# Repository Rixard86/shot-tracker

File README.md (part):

# ShotPuck: automatic arrow counter for Avalon barebow riser weights

A Ø40 × 10.4 mm puck that bolts onto the free face of an Avalon riser weight (the weight's own 5/16-24 bolt, one size longer, goes through its centre), detects each shot with a 6-axis IMU, records the bow's motion around it (accelerometer + gyroscope, 1.0 s before to 0.5 s after release), and reports both over BLE to the scoring app.

| | |
|---|---|
| Size / mass | Ø40 mm (= the Avalon barebow weight's diameter), 10.43 mm above the weight face (2.0 mm flat aluminium plate; the 1.2 mm PCB on 3 mm standoffs, the cell in a notch in the PCB), 17.1 g, centre of mass 0.5 mm off axis (no trim weight); 1.6 mm free space above the cell |
| Radio / MCU | u-blox BMD-340 (nRF52840, 1 MB flash / 256 KB RAM, PCB antenna), BLE 5 |
| Sensor | ST LSM6DSV32X IMU: 480 Hz, ±32 g accelerometer + ±2000 dps gyroscope while active; accelerometer only, 15 Hz wake-on-motion, while idle |
| Battery | LIR1254 Li-ion coin, 45–65 mAh, plain (no tabs) on spring contacts, protected by TI BQ29700 + DMN2004DWK; charged through a waterproof (IPX8) side-entry USB-C port, power only (21 mA, temperature-gated) |
| Firmware | Zephyr 4.1, custom board `shotpuck/nrf52840`, MCUboot 28 KB + signed app 201 KB (256 KB slots) / 107 KB RAM (58 KB of it the capture ring); captures compressed into a 408 KB flash area (D31) |
| Updates | Over the air: MCUboot with ECDSA-P256 signed images and automatic rollback, MCUmgr/SMP over BLE for paired phones, 10 s watchdog |
| Security / sync | Pairing required (LE Secure Connections); new phones only within 60 s of attaching the charger, which the advertising data signals so the app pairs by itself; links that do not encrypt within 30 s are dropped. Last ~900 shots kept in flash for replay. |

## Repository

```
layout.json                 shared geometry: CAD and PCB both read it
firmware/                   Zephyr app (src/, boards/shotpuck/, prj.conf, debug.conf)
firmware/sim/               Monte Carlo validation of src/shot_detect.c, unit tests of capture.c, evlog.c, chg_led.c, recovery.c, led_seq.c, wire.c, evq.c, the capture codec and store, and an end-to-end capture test (+ results.txt)
firmware/VERSION            firmware version (signed into the OTA image, shown in DIS and STATUS)
firmware/sysbuild.*         MCUboot + signing setup (refuses MCUboot's public dev key)
firmware/shotpuck_full.hex  MCUboot + signed app, for the first flash via the SWD test pads
firmware/shotpuck_update.bin  signed app image for OTA updates
hardware/design.py          the circuit (single source of truth)
hardware/design_mini.py     ShotPuck mini circuit: 33 x 33 mm square board for a Picatinny-rail case, CR2450 on the back
hardware/gen_sch.py         -> kicad/shotpuck.kicad_sch (`gen_sch.py design_mini` -> kicad/shotpuck-mini.kicad_sch)
hardware/check_netlist.py   KiCad netlist vs design.py (`check_netlist.py design_mini` for the mini)
hardware/gen_pcb.py         -> kicad/shotpuck.kicad_pcb (place, keep-outs, route, DRC)
hardware/gen_mini_pcb.py    -> kicad/shotpuck-mini.kicad_pcb (outline, CR2450 clip footprint, parts placed,
                            antenna keep-out, GND pours; unrouted, routed by hand, never overwritten)
hardware/board_shape.py     board outline, cell notch, bolt hole and antenna zone (shapely, from layout.json)
hardware/islands.py         post-fill GND island bridging used by gen_pcb.py
hardware/gen_bom.py         -> kicad/fab/shotpuck-bom.csv
hardware/gen_panel.py       -> kicad/panel/shotpuck-panel.kicad_pcb (1x2 KiKit panel for JLCPCB)
hardware/gen_jlc.py         -> kicad/fab/jlc/ (JLCPCB assembly BOM + CPL with LCSC part numbers, rotated/shifted to JLC's footprints)
hardware/bmd340.py          u-blox BMD-340 footprint, 3D model placement and schematic symbol (from its data sheet)
hardware/hotplug_sim.py     USB-C hot-plug simulation of the charge input, 324-case sweep (`--rev-0a`: R9 fed from VIN)
hardware/kicad/             KiCad project, ShotPuck.pretty/.kicad_sym/.3dshapes, schematic PDF, fab/ (gerbers, drill, pos, BOM)
mechanical/puck.py          CadQuery model + mass/balance -> out/ (STEP, STL, mass_report.txt);
                            geometry.py, puck_parts.py, puck_report.py hold its constants, parts and output
mechanical/plate_drawing.py plate manufacturing drawing (hole table, M2 thread callout) -> out/plate_drawing.pdf;
                            5052 sheet-metal prototype variant -> out/plate_drawing_5052.pdf + out/plate_5052.step
mechanical/plate_fdm.py     3D-printable (FDM) plate: locating lip instead of the O-ring, cell pocket, tube lip -> out/plate_fdm.stl
mechanical/viewer/          3D viewer of the rev 0A puck: assembled-to-exploded slider, cut view, cap seal band old/new
                            (three.js, one index.html with the meshes and the PCB embedded); also the private artifact claude.ai/artifact/EnhZPnRmLfCq5PVbHscZpo
mechanical/blender/         Blender scene + exploded-view assembly animation -> out/shotpuck_assembly.mp4/.blend
docs/PROTOCOL.md            BLE GATT protocol for the app
docs/VALIDATION.md          what is proven, and the on-device checklist
order/                      order packages for JLC (PCB + assembly, plate, cap), each with an ORDER.md:
                            form settings, notes for the order and the checks against JLC's rules
```

## Decisions (change any, then re-run the generators)

| # | Decision | Why | Alternative |
|---|---|---|---|
| D1 | **Cell beside the module, no trim weight** | Module at the upper right, bolt in the middle, cell in a notch at the bottom. The centre of mass is 0.5 mm off axis (≈ 0.01 mm on a 2 kg bow); Richard dropped the optional brass pin when the PCB went up on standoffs | Two LIR1254 side by side (studied: they cut the board in two); a brass trim pin |
| D2 | **Flat 6061 plate (2.0 mm) + polycarbonate cap, bolted on through a steel sleeve** | Richard: the v0.2 stud could not be fitted to the bow (it needs a bolt from above), and a flat plate is cheaper (laser or waterjet, no turning). The sleeve carries the bolt's clamp load to the plate; on the prototype the PC cap top sits between the bolt head and the sleeve (D21) | Turned 7075 base with an integral stud (v0.2) |
| D3 | **nRF52840 in high-voltage mode** (cell → VDDH, REG0 = 3.0 V) | No regulator, no battery divider (internal VDDH/5), fewer leaks | External LDO |
| D4 | **MCP73831 + firmware temperature gate** (nRF die temperature, <1 °C / >44 °C) | MCP73831 programs down to 15 mA; the TS-pin chargers found start at 100 mA. Default is *charging allowed* if the MCU is dead, so a flat cell always recovers. | Charger with an NTC input and a thermistor at the cell |
| D5 | **32 kHz from internal RC; REG1 in DC/DC mode in the app (0.3.1), REG0 and MCUboot in LDO mode** | The BMD-340 has no 32.768 kHz crystal. Its data sheet (UBX-19033353 §3.3) puts an LDO and a DC/DC converter with no external parts in both regulator stages, and DC/DC about halves the CPU and radio current. REG0 also feeds the IMU, so it stays LDO until its noise is checked; MCUboot stays LDO so an OTA image with DC/DC can roll back | All LDO (0.3.0); DC/DC on REG0 as well |
| D6 | **Plain LIR1254 (no tabs) on contacts:** a + spring against the can side and a − strap over the top cap, soldered to two SMD pads left of the notch; the cap's foam pad clamps the cell and the strap | Richard's choice: no tab variant to source, no soldering on the cell, swappable | Tabbed LIR1254 soldered to pads; 601015 pouch (closed-ring board, ~9.9 mm) |
| D7 | **Pairing required; new pairings only within 60 s of attaching the charger** (LE Secure Connections Just Works, up to 4 phones, FORGET_BONDS to reset) | Several pucks and shooters at one club: other apps must not read, reconfigure or reset your puck. The charger gesture proves physical possession. | Open access (v1), or a PIN shown by LED blinks |
| D8 | **Detector thresholds are defaults, tunable over BLE**; every candidate is reported | Real release-shock data is unknown until you shoot | – |
| D9 | IMU rotated 270°, reference designators on F.Fab only | Routability; board too dense for silkscreen text | – |
| D10 | **LSM6DSV32X IMU** (LSM6DSV32XTR, C22461202, since 2026-10-01; v0.2 used the LSM6DSO32, which replaced the LIS2DE12 accelerometer). Same LGA-14 pinout and land pattern as the LSM6DSO32, so the board is unchanged; JLC's footprint lands within 0.013 mm of ours at 0°. Pinout, pin states and register values checked against datasheet DS13511 Rev 2 and ST's `lsm6dsv32x_reg.h`. It has no separate I3C disable, so the I²C anti-spike filter is forced on at init (`IF_CFG.ASF_CTRL`), as the datasheet describes for I²C-only use. It has no 416 Hz rate: ACTIVE runs at 480 Hz | Gyroscope for bow rotation; ±32 g clips the release shock less; 2.75× lower accelerometer noise than the LSM6DSO32 at ±32 g (80 against 220 µg/√Hz) and lower gyroscope noise (2.8 against 3.8 mdps/√Hz); ±4000 dps available; 5,864 in JLC stock against 177 | LSM6DSO32XTR (C3663738): 416 Hz, twice the FIFO (3 KB uncompressed), 0.1 mA less while active |
| D11 | **Raw 6-axis capture per accepted shot** (standard −1.0 s to +0.5 s, 720 samples, 8.6 KB raw; extended −6 s to +2 s, D31), analysed in the app | Which bow-movement metrics matter is unknown until real shots are recorded | On-device metrics (cant, steadiness, post-release rotation) in the EVENT |
| D12 | **Identity from the chip's factory ID**: name `ShotPuck-XXXX`, DIS serial number = `device_id` | Tell pucks apart at a club; one stable ID across phones for PowerSync | App-assigned IDs |
| D13 | **Accepted shots in a 32 KB flash ring** (~900 shots), rejected candidates in RAM; app-driven REPLAY, sent paced in the background | Shots survive dropouts and resets without per-phone sync state on the puck | Device push with ACK (rejected: shared state, first phone drains the backlog); captures in flash too |
| D14 | **u-blox BMD-340-A-R (nRF52840) instead of the Raytac MDBT50Q-1MV2**: 15.0 × 10.2 × 1.9 mm LGA-68, PCB antenna, VCCH input for high-voltage mode, FCC/CE/Bluetooth certified. Footprint `ShotPuck:u-blox_BMD-340` from data sheet UBX-19033353 (Figure 12), checked pad for pad against two built open-source footprints | Richard: replace parts JLCPCB does not stock. On 2026-09-29 JLCPCB had 0 MDBT50Q-1MV2 and 227–393 BMD-340 (C5456944, $8.73 vs $18.93). nRF52840 kept for the two OTA slots (2 × 460 KB). **Only type BMD-340-A-R-10 is usable:** -00 (nRF52840 rev 1) has a non-functional high-voltage mode, so confirm the type with JLCPCB before ordering | MDBT50Q-1MV2 via global sourcing or consignment; u-blox NINA-B306 ($20, 59 in stock) |
| D16 | **Cell protection (PCM): TI BQ29700 + Diodes DMN2004DWK** in the cell's negative lead (OVP 4.275 V, UVP 2.80 V, ±0.1 A over-current, short-circuit) | LIR cells have no protection of their own; kept from the CP1654 design (BQ29700 was on Varta's list). Costs 4 µA standby | – |
| D17 | **1.6 mm free space above the cell** (7.0 mm from the Kapton to the ceiling) | No swell spec for LIR cells. It was 1.2 mm (set on the magnetic board so its connector was flush with the cap top, D25) until the PCB went to 1.2 mm (D30): the ceiling rose 0.4 mm with the board, so the free space is now above Varta's 1.5 mm. The foam pad fills it | 1.2 mm with 2.6 mm standoffs (non-stock) |
| D19 | **Board Ø36 mm; 4× M2×8 cheese head (Torx) screws from above, all at r = 16.5 mm: H1 100.6°, H2 164.5°, H3 305°, H4 226°**, through the cap, PCB and standoffs into the tapped plate | Puck Ø40 mm is fixed by the Avalon weight; 36 leaves 0.5 mm fit clearance. The screws sit clear of the module, the cell notch and the port. H1 and H2 sit either side of the USB-C port, far enough apart that the ground pour reaches J1's wing tabs; H4 holds the left arm (D29). The 1.3 mm head lets an M2×8 end 0.1 mm inside the plate (a socket head would need the non-standard M2×7). Since 2026-10-12 the screws are M2×5 into brass male-female standoffs screwed into the plate; the cap keeps the M2×8 counterbore | – |
| D20 | **Cell in a notch in the PCB, open to the rim** (Ø13.0 mm round end), on the Kapton over the plate | Saves the 0.8 mm board in height. Richard preferred the notch to a closed hole | Closed hole (holds the cell all round, leaves a thin strip at the rim) |
| D18 | **Waterproof (IPX8) side-entry USB-C, SHOU HAN TYPE-C 6PFS 2JCB1.6-H6.7 IPX8** (6-pin, power only, LCSC C3020041, JLC-assembled) at 132.58° on the left rim, recessed in a notch in the board edge, plug axis radial through the cap wall; R10/R11 5.1k pull CC1/CC2 down | Richard (2026-09-30). Any USB-C charger and cable fits, JLC places the part (the magnetic one was hand-soldered), and its own silicone ring seals it in the cap wall. The CC pull-downs make USB-C chargers switch on 5 V | Samzo PR5L4015 magnetic receptacle flush with the cap top (the magnetic board, last at commit `01f2e00`) |
| D15 | **OTA = MCUboot swap-using-move + MCUmgr SMP over BLE**, ECDSA-P256 signed, encrypted link (paired phones) only. A new image runs on trial and confirms itself once a paired phone has connected over an encrypted link and it has run 10 s (so an image that runs but cannot talk BLE rolls back); a 10 s hardware watchdog turns a hang into a reset, and MCUboot then rolls back | Standard Nordic/Zephyr path; the Flutter app can use Nordic's `mcumgr_flutter` | Firmware-loader mode (single slot); no rollback |
| D21 | **One loose steel tube from the plate through the PCB to the underside of the cap top, located by a lip under the cap** (Richard, prototype) carries the bolt load from the cap top to the plate; the PCB hole (Ø10.4: 0.2 mm clearance covers JLCPCB's ±0.2 mm outline tolerance) is merged into the cell notch | Richard: the tube must not get lost while the puck is off the bow. Bonded into the cap and standing 0.1 mm proud, it was held by 1.2 mm of glue that the stack tolerance between cap and plate (±0.15–0.3 mm) and the bolt's squeeze would break at the first bolt-up, and then it could slide out through the top. Trapped between the plate and the cap it cannot fall out and needs no glue. **Known risk, tested on the prototype:** the bolt clamps the 1.33 mm PC cap top onto the tube end. At 3 N·m (~2 kN) that is 80–110 MPa on the tube end, at PC's compressive yield, so the cap top may creep and the bolt lose preload (VALIDATION §2). Everything right of the merged hole is copper-free (D22), so no signal has to cross it. No stock insulating tube fits (glass-epoxy 10 × 8 mm grips a 5/16 bolt, plastics creep), so it is steel, with Kapton tape all round it because it can turn | Tube bonded into the cap, 0.1 mm proud (glue breaks, tube can fall out); turned sleeve with a collar in a recess under the cap top (steel-only clamp path, custom part); tube bonded into the plate; sleeve on the PCB with a spacer below (PCB in the clamp path) |
| D22 | **On-board PCB antenna** (BMD-340), module at the upper right with its antenna end pointing 45° below +x; the antenna zone (from 4.4 mm inside the module's end) and everything right of the tube are copper-free (`board_shape.rf_keepout`) | Richard's choice over moving the antenna out into the cap. The module slid 45° around the tube so the USB-C port fits on the left | Module with a u.FL connector and an antenna in the cap |
| D23 | **SWD on 4 bottom test pads** (VDD, SWDIO, SWDCLK, GND, 2.54 mm pitch, under the module) for a pogo-pin jig | Frees top-side space for 2-layer routing; the SWD escape vias are pre-placed | Tag-Connect TC2030-CTX-NL (v0.2) |
| D24 | **I2C on internal pull-ups only; SCL = P0.07, SDA = P0.05** (BMD-340 pads 23 and 21, facing the IMU) | The 4.7k DNP pads (R5/R6) were never fitted and cost routing space; the swap stops the IMU lines crossing on 2 layers | Keep R5/R6 as DNP pads for a stronger pull-up |
| D25 | **PCB on 3 mm standoffs; puck 10.43 mm** | Set on the magnetic board so its connector sat flush with the cap top, and kept. The cap top went from 1.2 to 1.33 mm (2026-09-30, Richard) so 0.80 mm of it is left over the USB-C body, JLC3DP's minimum SLA wall for a ~10 mm feature. The cell sets the ceiling, so the raised board costs no height, and it keeps the antenna 3 mm further from the plate | Board on the plate |
| D26 | **Button head bolt** (5/16-24, dome head Ø16.7 × 4.4 mm, ISO 7380 style), no washer | Richard: lower head than a socket head (7.9 mm). The head bears directly on the PC cap top (163 mm², ~12 MPa at 2 kN) and clamps it onto the sleeve (D21) | Socket head cap screw |
| D27 | **Charge-input protection: SMF5.0CA bidirectional TVS (D3) at the connector + R9 1k / C9 100n in front of the nRF VBUS pin** | The port is exposed (ESD) and plugging in makes and breaks contact (hot-plug spikes); the TVS is bidirectional and sits before D1. The SMF5.0CA starts clamping at 6.4–7.0 V (200 W) against the MCP73831's 7 V absolute maximum. No 5 V TVS can hold the nRF52840 VBUS pin under its 5.8 V absolute maximum; it is used only to detect the charger (~24 µA), so the RC limits current into it and smooths spikes. R9 is fed from VIN_RAW, before D1 (rev 0B, since 2026-10-12; rev 0A boards feed it from VIN): fed from VIN, D1 and C1 hold a plug-in overshoot for milliseconds and the RC passes it on (hot-plug simulation: VBUS_SNS up to 6.36 V, against ≤ 5.47 V fed from VIN_RAW). It sat on VIN because the magnetic board's hand-wired lead could be reversed; a USB-C plug cannot reverse VBUS | PESD5V0S1BB (a signal-line ESD diode, clamps only from 5.5–9.5 V); unidirectional flat-clamp TVS after D1 (TI TVS0500); an overvoltage switch (needed only if 9–12 V adapters are a risk) |
| D28 | **Routing aids for 2 layers (BMD-340):** module pins chosen so its second pad column escapes through the outer column's gaps towards the IMU; links and vias locked before Freerouting (`PRE_LINKS`, `PAD_BRIDGES`, `PRE_VIAS` rotated with the module, `PRE_ROUTED` in `gen_pcb.py`) | The LGA module's inner pads need planned escapes. Everything right of the tube is copper-free (D22), so no VIN loop or passage is needed (`VIN_ESCAPE = None`). The board routes with 0 DRC / 0 unconnected; J1's notch and a few fixes are hand edits (Build & flash) | 4 layers |
| D29 | **Shot shock: 4th screw H4 on the left arm; BMD-340 and C2 corner-staked** (Richard) | The slot for the cell and the tube makes the board a horseshoe. Its left arm (PCM, both cell contact pads) had no screw below H2. The model below is of the magnetic board (H1 then at (9.2, 1.2)) and was not re-run for the USB-C layout, whose board is also clamped through rubber O-rings. A plate model of the board (Kirchhoff plate FE, 100 g along the puck axis, component masses, module 1–5× stiffer than the board) gives, at 0.8 mm: first mode 1.1–1.2 kHz → 1.7–2.0 kHz; worst strain 320–340 → 160–180 µε (bare board next to a screw; ≤ 70 µε at any part); the − cell pad moved 13–15 µm against the cell per 100 g, now ~0. At 1.2 mm with 4 screws (the board now, D30): 2.7–3.2 kHz, ~100 µε | Foam pad under the board (damping, no layout change); thicker PCB alone (1.2 mm, 3 screws: 1.7–1.8 kHz) |
| D30 | **PCB 1.2 mm** (was 0.8), stock 3 mm standoffs, puck 0.4 mm taller (10.43 mm) | Richard (2026-09-30): a stiffer board under shot shock (D29: first mode 1.7–2.0 → 2.7–3.2 kHz, strain about halved). Everything on the board rose 0.4 mm, so the cell ceiling (`cell.swell_h` 6.6 → 7.0) and the cap rose with it and every cap, lip and port clearance is unchanged; the tube is 7.1 mm | 0.8 mm board (puck 10.03 mm); 1.2 mm on 2.6 mm standoffs (non-stock) to keep 10.03 mm |
| D31 | **Captures compressed into a 408 KB flash area, plus an extended capture mode** (firmware 0.3.0): lossless delta/slope + Rice coding per 32-sample block, newest captures push out the oldest; CONFIG `capture_mode` picks standard (−1.0..+0.5 s) or extended (−6..+2 s) | Richard (2026-11-08): 72 captures (a full round) should survive offline sessions, and about 12 long captures should show the whole shot routine. The update slots shrank from 460 to 256 KB to make room (app 205 KB). The shot log stays separate and unchanged: shot records are 32 B, so sharing one pool would gain only 5–8 captures | External SPI flash (no room on the board); sharing one pool with the shot log; dropping the second update slot (no rollback) |

## Needs your input before ordering

1. **USB-C port:** JLC-assembled (C3020041, D18); charge with any 5 V USB-C charger and cable. Ask JLC to confirm the part is in stock for the order.
2. **LIR1254:** buy a plain cell (no tabs) from a maker with a datasheet. Check its charge voltage (ours 4.20 V) and that 21 mA (R1 = 47k) is within its standard charge current (usually 0.5 C).
3. **Cell contacts:** not a bought part yet. For prototypes, form the + spring and the − strap from 0.15 × 2 mm nickel strip (as in the animation) and put Kapton tape where the strap passes the can edge.
4. **Bolt:** a 5/16-24 button head socket cap screw, longer than the original Avalon bolt by the puck height (10.43 mm). Check that length is sold in 5/16-24 and the thread engagement in the riser; don't over-tighten (3/16 in hex).
5. **Component masses:** weigh the real parts, put them in `layout.json`, and re-run `puck.py` for the mass report.
6. **Back up the OTA signing key** `%USERPROFILE%\.shotpuck\ota-signing-key.pem` (password manager or offline copy). Pucks accept only images signed with it: if it is lost, updates need a cable (SWD); if it leaks, anyone who can pair could install their firmware. It is never committed (`*.pem` is git-ignored).
7. **Module type:** before ordering, ask JLCPCB support to confirm that their BMD-340-A-R stock (C5456944) is type **BMD-340-A-R-10**. Types -00 and -01 are obsolete, and -00's nRF52840 rev 1 silicon makes high-voltage mode unusable (D14).
8. **O-rings:** buy 36, 37 and 38 × 1.0 mm (VMQ or NBR, 70 Shore A) for the cap seal and 2 × 1.0 mm for the four screws; fit them on the first SLA cap (resin shrink moves the ledge) and tune `seal.ledge_od`/`squeeze` in `layout.json`.

## Simulation results (`firmware/sim/results.txt`, seed 2026)

| Set | Shots | Recall | Precision | Notes |
|---|---|---|---|---|
| Nominal sessions | 437 | 99.1 % | 99.8 % | walking knocks, set-downs, stand knocks, nock taps, drops, let-downs (1 FP: stand knock) |
| Hard cases | 479 | 99.6 % | 99.4 % | + taps while aiming, hard grabs off the stand (2 grabs, 1 stand knock) |
| Weak bow (info) | 253 | 80.2 % | 99.5 % | 4–12 g shock, 5–30° rotation: **thresholds must be tuned on real shots** |

The detector needs three things together: a high-frequency shock (6 g sample-to-sample), ≥ 0.5 s of stillness before it (aiming), and ≥ 250 mg of low-frequency bow motion 0.1–0.6 s after it (bow jump into the sling). See `firmware/src/shot_detect.h`. It uses the accelerometer only; the gyroscope feeds the capture.

## Battery life (estimate, verify via JP1)

The idle draw is roughly 14 µA (LSM6DSV32X accelerometer in low-power mode 1 at 15 Hz, about 7 µA by interpolating the datasheet's 4.0 µA at 1.875 Hz and 17 µA at 60 Hz; BQ29700 protection 4 µA; nRF System ON + RC). While active it is roughly 0.8–0.9 mA: the accelerometer and gyroscope together are about 0.65 mA, plus 480 Hz FIFO reads and the BLE link. At **2 h of training per day** that is ≈ 2.0 mAh/day, so roughly **3–4.5 weeks per charge** from a 45–65 mAh LIR1254 (a little less, as the 3.3 V cut-off leaves some capacity unused). A full charge at 21 mA takes about 2.5–3.5 h. The low-battery cut-off (3.3 V, three readings in a row since 0.3.1: about 30 s while active, 3 min while idle) puts the puck into System OFF until the charger is attached.

## Build & flash

Native Windows toolchain (what v0.2 was built and verified with):

| Tool | Where | Used for |
|---|---|---|
| KiCad 10.0 | `C:\Program Files\KiCad\10.0` (its `python.exe` has `pcbnew`) | schematic, PCB, ERC, DRC, fab exports |
| Freerouting 2.1.0 + Java 21 | `%USERPROFILE%\tools\freerouting-2.1.0.jar`, `%USERPROFILE%\tools\jre21` (or set `FREEROUTING_JAR`, `JAVA`) | PCB routing |
| Zephyr v4.1.0 workspace + SDK 0.17.0 | `C:\zp` (west, modules `cmsis`, `cmsis_6`, `hal_nordic`, `segger`, `hal_st`, `mbedtls` for pairing crypto, `mcuboot` + `zcbor` for OTA) | firmware |
| CMake 3.31 + Ninja | `%USERPROFILE%\tools\cmake3`, `%USERPROFILE%\tools\ninja` (Zephyr 4.1 fails with CMake 4.x) | firmware |
| w64devkit gcc | `%USERPROFILE%\tools\w64devkit` (set `CC` to its `gcc.exe`) | simulation, capture tests |

**Firmware** (Zephyr 4.1 sysbuild: MCUboot + signed app in one build):

```
set ZEPHYR_BASE=C:\zp\zephyr
set ZEPHYR_SDK_INSTALL_DIR=C:\zp\zephyr-sdk-0.17.0
set PATH=%USERPROFILE%\tools\cmake3\bin;%USERPROFILE%\tools\ninja;C:\zp\.venv\Scripts;%PATH%
cd C:\zp
west build --sysbuild -p always -b shotpuck/nrf52840 <repo>/firmware -d build\sb -- ^
  -DBOARD_ROOT=<repo>/firmware ^
  -DSB_CONFIG_BOOT_SIGNATURE_KEY_FILE=\"C:/Users/<you>/.shotpuck/ota-signing-key.pem\"
python zephyr\scripts\build\mergehex.py -o shotpuck_full.hex build\sb\mcuboot\zephyr\zephyr.hex build\sb\firmware\zephyr\zephyr.signed.hex
```

- The key path needs the escaped quotes (Kconfig string). Without the private key the build stops on purpose instead of signing with MCUboot's public dev key.
- **First flash** (bootloader + app) by cable: `shotpuck_full.hex` with J-Link/nrfjprog through the 4 SWD test pads on the bottom (VDD, SWDIO, SWDCLK, GND at 2.54 mm; pogo-pin jig or pogo probes), before the board goes onto the plate.
- **Updates over the air:** `build\sb\firmware\zephyr\zephyr.signed.bin` (copied to `firmware/shotpuck_update.bin`), sent from a paired phone (your app with `mcumgr_flutter`, or Nordic's nRF Connect Device Manager). Bump `firmware/VERSION` for every release.
- **0.2.x → 0.3.0 by cable only:** 0.3.0 changed the flash layout (D31), which the bootloader holds. Flash 0.2.x pucks once with `shotpuck_full.hex` over SWD; never send 0.3.0 over the air to a 0.2.x puck.
- RTT logging build: add `-DEXTRA_CONF_FILE=debug.conf`. It fits the slot (237 of 248 KB) and can be installed over the air too. Since 0.3.0 it has no `CONFIG_ASSERT`: with asserts it no longer fits the 256 KB slots.
- The first boot programs UICR REGOUT0 = 3.0 V and resets once.
- Generate a new signing key only for a new product line: `python C:\zp\bootloader\mcuboot\scripts\imgtool.py keygen -k ota-signing-key.pem -t ecdsa-p256`. Pucks flashed with one key never accept images signed with another.

**Simulation + unit tests:** `set CC=%USERPROFILE%\tools\w64devkit\bin\gcc.exe` then `python firmware/sim/simulate.py --sessions 36 --stress --seed 2026` (needs numpy, scipy). Must print `CAPTURE TESTS: PASS`, `EVLOG TESTS: PASS`, `CHG LED TESTS: PASS`, `RECOVERY TESTS: PASS`, `CODEC TESTS: PASS`, `CAPSTORE TESTS: PASS`, `CAPWRITER TESTS: PASS`, `CAPWRITER FAULT TESTS: PASS`, `LED SEQ TESTS: PASS`, `WIRE TESTS: PASS`, `EVQ TESTS: PASS` and `RESULT: PASS`.

**Hardware** (run with KiCad 10's Python, from `hardware/`):

```
"C:\Program Files\KiCad\10.0\bin\python.exe" gen_sch.py
"C:\Program Files\KiCad\10.0\bin\python.exe" check_netlist.py      # must print PASS
kicad-cli sch erc --severity-all -o kicad\erc.rpt kicad\shotpuck.kicad_sch
"C:\Program Files\KiCad\10.0\bin\python.exe" gen_pcb.py --no-route  # placement only, then DRC
"C:\Program Files\KiCad\10.0\bin\python.exe" global_route.py       # routability estimate: overflow + hotspots
"C:\Program Files\KiCad\10.0\bin\python.exe" gen_pcb.py --quick     # one-attempt trial route (~5 min)
"C:\Program Files\KiCad\10.0\bin\python.exe" gen_pcb.py            # place, route, bridge GND islands, DRC
"C:\Program Files\KiCad\10.0\bin\python.exe" gen_bom.py
kicad-cli pcb export gerbers -o kicad\fab\gerbers -l F.Cu,B.Cu,F.Paste,B.Paste,F.Silkscreen,B.Silkscreen,F.Mask,B.Mask,Edge.Cuts --subtract-soldermask kicad\shotpuck.kicad_pcb
kicad-cli pcb export drill -o kicad\fab\gerbers --excellon-separate-th --generate-map --map-format gerberx2 kicad\shotpuck.kicad_pcb
kicad-cli pcb export pos --format csv --units mm --side both -o kicad\fab\shotpuck-pos.csv kicad\shotpuck.kicad_pcb
```

Zip `kicad\fab\gerbers\` into `kicad\fab\shotpuck-gerbers.zip`. The single board is for reference: JLCPCB gets the panel (below). The pos file is in KiCad page coordinates, with the bolt axis at (132.064, 91.396) and Y negated. Don't set a drill/place origin to change that: it breaks KiKit's panel frame (HANDOVER §7).

Hot-plug check (plain Python with numpy and scipy, from `hardware/`, about 1 min): `python hotplug_sim.py` must report `VBUS_SNS > 5.8 V in 0` and `VIN > 7.0 V in 0`; `python hotplug_sim.py --rev-0a` models the rev 0A boards (9 cases over 5.8 V, README D27).

Freerouting routes the signals only (GND comes from the pours, fan-out and stitching vias) and is not deterministic. `gen_pcb.py` re-routes up to 4 times until nothing is unconnected; if it still does not end with `0 DRC violations` and `0 unconnected pads`, run it again. ERC: 0 errors; the 2 warnings are the intentional straps of LSM6DSV32X SA0 and SDx to GND.

**Hand edits:** `gen_pcb.py` does not draw J1's board-edge notch (10.28 × 5.22 mm with two Ø0.70 NPTH leg holes), and the GND via at (−0.41, 16.09), the JP2 reset pads and the silkscreen text were added by hand in KiCad; U2, C3, C6 and C7 were moved inward by hand, away from the top panel tab. Re-running `gen_pcb.py` overwrites the board without them, so back it up and redo them (HANDOVER §6).

**Mechanical:** `C:\zp\.cq\Scripts\python.exe mechanical/puck.py` (CadQuery 2.8 in a Python 3.12 venv; CadQuery has no Python 3.14 wheels). It writes the mass and balance report; there is no trim weight. `C:\zp\.cq\Scripts\python.exe mechanical/plate_drawing.py` writes the plate drawing (`out/plate_drawing.pdf`) from the same `layout.json`, and the cheaper prototype variant in 5052 sheet (`out/plate_drawing_5052.pdf` + `out/plate_5052.step`, no chamfer). `C:\zp\.cq\Scripts\python.exe mechanical/plate_fdm.py` writes the 3D-printable plate (`out/plate_fdm.stl`).

**3D viewer:** open `mechanical/viewer/index.html` in a browser (it needs internet for three.js from jsDelivr; everything else, the PCB included, is inside the file). It is a snapshot: the cap, plate and sleeve meshes and the layout values were embedded on 2026-10-12 and the PCB is the rev 0A board (KiCad's export, with its green mask recoloured to the ordered black, the silkscreen opaque white and the FR4 core dark and opaque), so edit it (or rebuild it) when those change.

**Assembly animation (Blender 3.1+):** `"C:\Program Files\Blender Foundation\Blender 3.1\blender.exe" -b -P mechanical/blender/render_assembly.py` (after `puck.py`; it exports the populated board from KiCad as GLB itself). It renders an exploded view that assembles into the puck (Cycles on the GPU, 1080p, 13 s) to `mechanical/out/frames/` and encodes `mechanical/out/shotpuck_assembly.mp4`; the scene is saved as `shotpuck_assembly.blend`. Add `-- --preview` for 5 half-size stills, `-- --encode` to re-encode existing frames. Existing frames are skipped, so an interrupted render resumes; when `layout.json`, the STLs, the board, its 3D models or the Blender scripts have changed since the frames were made (`frames/scene.sha256`), they are deleted first. The cell and its contacts, standoffs, M2 screws, button head bolt, the seal and clamp O-rings, Kapton and foam are modelled from `layout.json`; the board parts, including the USB-C port, use KiCad's 3D models.

**Panel + JLCPCB assembly files** (after `gen_pcb.py`, with KiCad 10's Python and KiKit: `python.exe -m pip install --user kikit`):

```
"C:\Program Files\KiCad\10.0\bin\python.exe" gen_panel.py      # 1x2 in a frame, 4 tabs per board, mouse bites, fiducials, tooling holes
"C:\Program Files\KiCad\10.0\bin\python.exe" gen_jlc.py        # kicad/fab/jlc/shotpuck-panel-bom.csv + -cpl.csv
kicad-cli pcb export gerbers -o kicad\fab\panel\gerbers -l F.Cu,B.Cu,F.Paste,B.Paste,F.Silkscreen,B.Silkscreen,F.Mask,B.Mask,Edge.Cuts --subtract-soldermask kicad\panel\shotpuck-panel.kicad_pcb
kicad-cli pcb export drill -o kicad\fab\panel\gerbers --excellon-separate-th --generate-map --map-format gerberx2 kicad\panel\shotpuck-panel.kicad_pcb
```

Zip `kicad\fab\panel\gerbers\` into `shotpuck-panel-gerbers.zip`. The drill is split into `-PTH.drl` (vias) and `-NPTH.drl` (mouse bites, J1 legs, tooling, screw holes), as JLCPCB asks. Each comes with a `-drl_map.gbr` drill map, which JLC's KiCad guide asks for. Do not refill the zones on export: the panel's saved fill is the one DRC checked. `gen_jlc.py` rotates and shifts U1 (BMD-340, +2.0 mm to its pad-array centre), U3, Q1, Q2 (+270°), D4 (+180°, JLC's pad 1 is its cathode on the other side), D3 (+180°, JLC numbers its pads the other way; the TVS is bidirectional, so this only fixes the preview) and J1 (0.15 mm) so JLC's own footprints land on ours; this was checked pad by pad against the EasyEDA footprints of the LCSC parts.

## Fabrication & assembly

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
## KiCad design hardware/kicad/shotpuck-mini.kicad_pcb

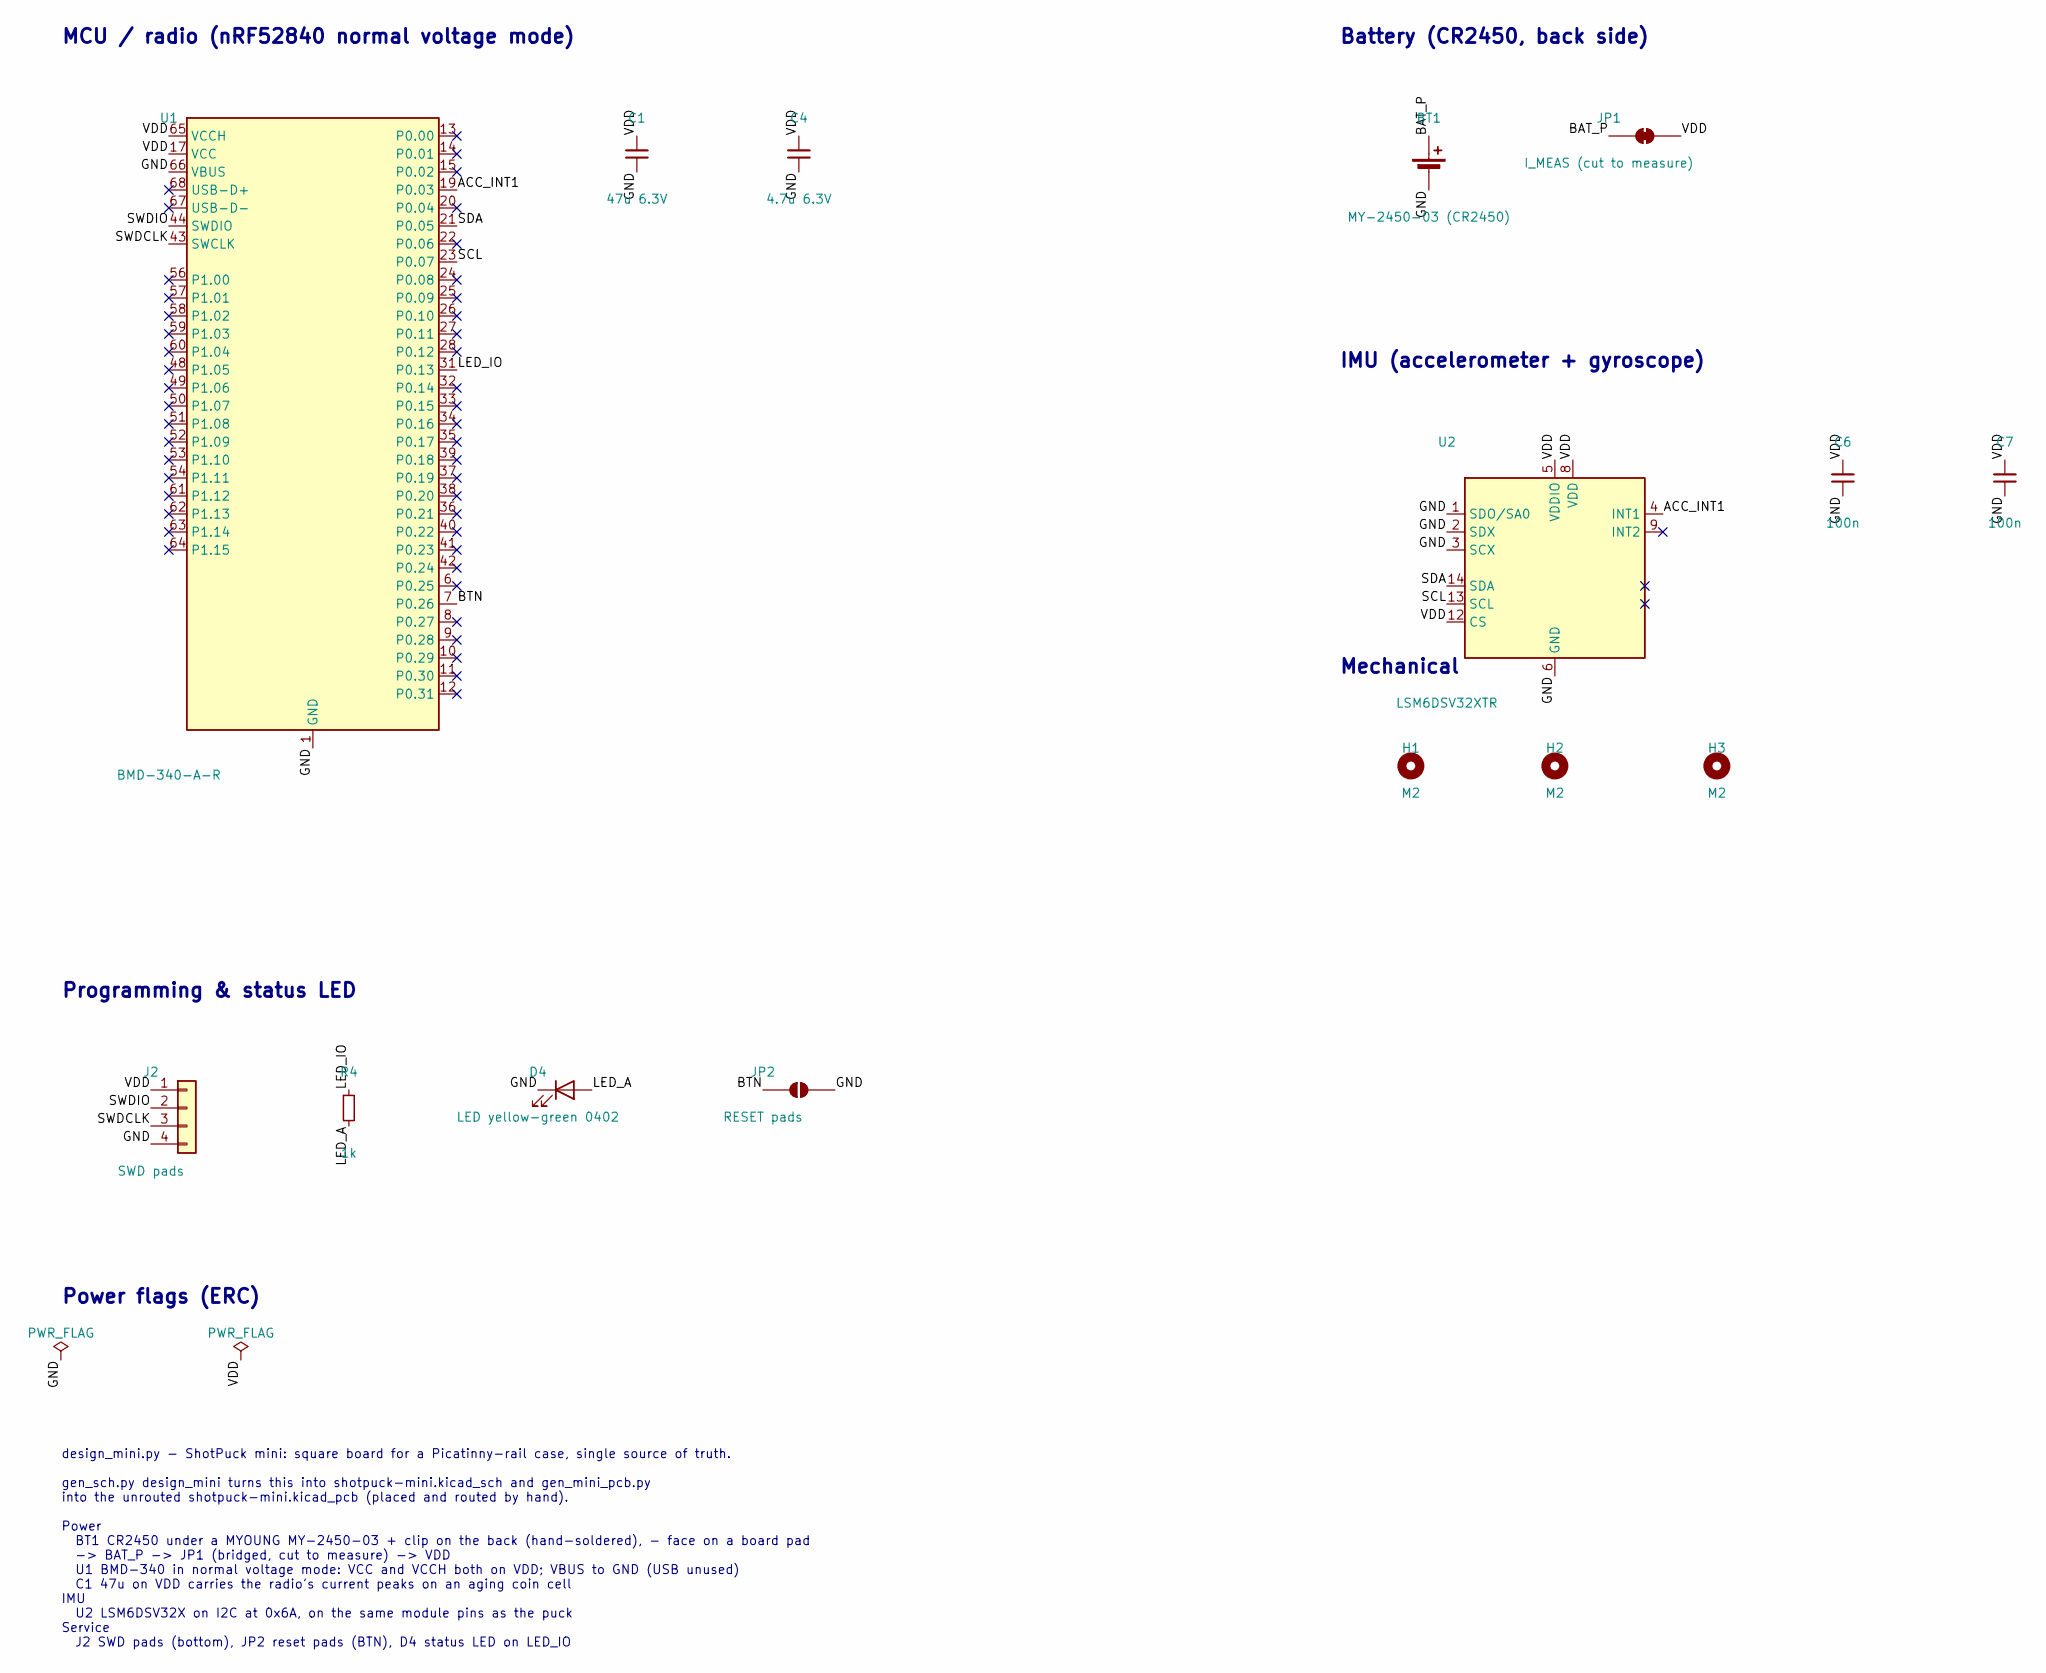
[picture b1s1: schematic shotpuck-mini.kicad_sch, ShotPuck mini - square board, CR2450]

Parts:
BT1: MY-2450-03 (CR2450); BatteryHolder_MYOUNG_MY-2450-03_CR2450
C1: 47u 6.3V; C_0805_2012Metric
C4: 4.7u 6.3V; C_0402_1005Metric
C6, C7: 100n; C_0402_1005Metric
D4: LED yellow-green 0402; LED_0402_1005Metric
H1, H2, H3: M2; MountingHole_2.4mm_NPTH
J2: SWD pads; SWD_Pads_1x4_P2.54
JP1: I_MEAS (cut to measure); SolderJumper-2_P1.3mm_Bridged_Pad1.0x1.5mm
JP2: RESET pads; TweezerPads_2x0.8mm_Gap0.4mm
R4: 1k; R_0402_1005Metric
U1: BMD-340-A-R; u-blox_BMD-340
U2: LSM6DSV32XTR; LGA-14_3x2.5mm_P0.5mm_LayoutBorder3x4y

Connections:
/ACC_INT1: U1.19 (P0.03), U2.4 (INT1)
/BAT_P: BT1.1 (+), JP1.1 (A)
/BTN: JP2.1 (A), U1.7 (P0.26)
/GND: BT1.2 (-), C1.2, C4.2, C6.2, C7.2, D4.1 (K), J2.4, JP2.2 (B), U1.1 (GND), U1.2 (GND), U1.3 (GND), U1.4 (GND), U1.5 (GND), U1.16 (GND), U1.18 (GND), U1.29 (GND), U1.30 (GND), U1.45 (GND), U1.46 (GND), U1.47 (GND), U1.55 (GND), U1.66 (VBUS), U2.1 (SDO/SA0), U2.2 (SDX), U2.3 (SCX), U2.6 (GND), U2.7 (GND)
/LED_A: D4.2 (A), R4.2
/LED_IO: R4.1, U1.31 (P0.13)
/SCL: U1.23 (P0.07), U2.13 (SCL)
/SDA: U1.21 (P0.05), U2.14 (SDA)
/SWDCLK: J2.3, U1.43 (SWCLK)
/SWDIO: J2.2, U1.44 (SWDIO)
/VDD: C1.1, C4.1, C6.1, C7.1, J2.1, JP1.2 (B), U1.17 (VCC), U1.65 (VCCH), U2.5 (VDDIO), U2.8 (VDD), U2.12 (CS)

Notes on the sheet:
MCU / radio (nRF52840 normal voltage mode)
Programming & status LED
Battery (CR2450, back side)
IMU (accelerometer + gyroscope)
Mechanical
Power flags (ERC)
design_mini.py - ShotPuck mini: square board for a Picatinny-rail case, single source of truth. gen_sch.py design_mini turns this into shotpuck-mini.kicad_sch and gen_mini_pcb.py into the unrouted shotpuck-mini.kicad_pcb (placed and routed by hand). Power BT1 CR2450 under a MYOUNG MY-2450-03 + clip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

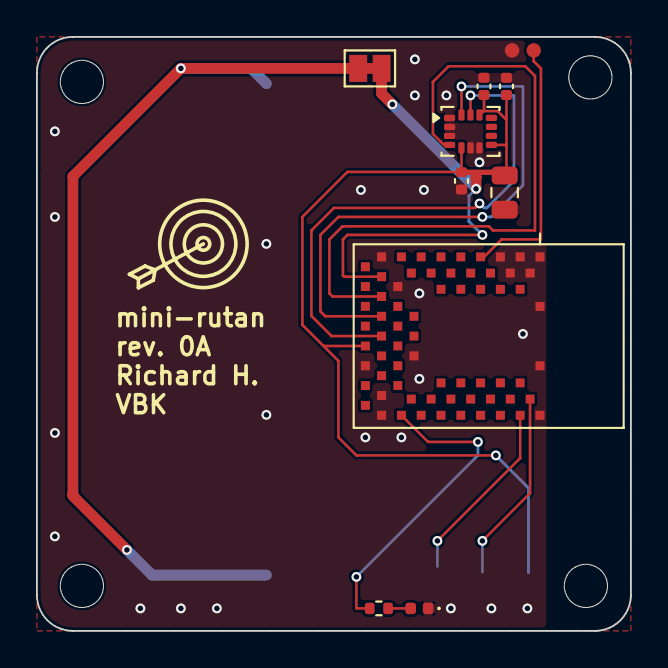
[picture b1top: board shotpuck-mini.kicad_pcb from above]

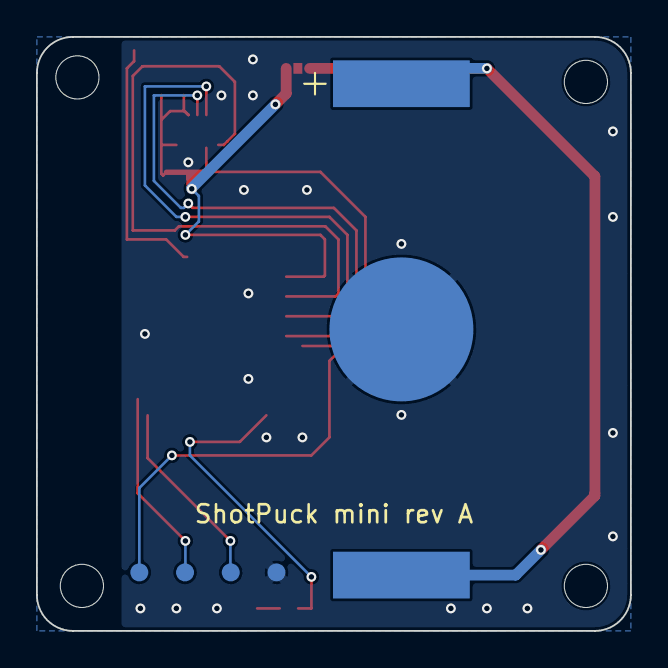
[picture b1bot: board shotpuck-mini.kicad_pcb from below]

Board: 2 copper layers, 33.0 x 33.0 mm, 16 parts (2 on the bottom side), 11 nets.

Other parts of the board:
H3#2: M2; MountingHole_2.4mm_NPTH

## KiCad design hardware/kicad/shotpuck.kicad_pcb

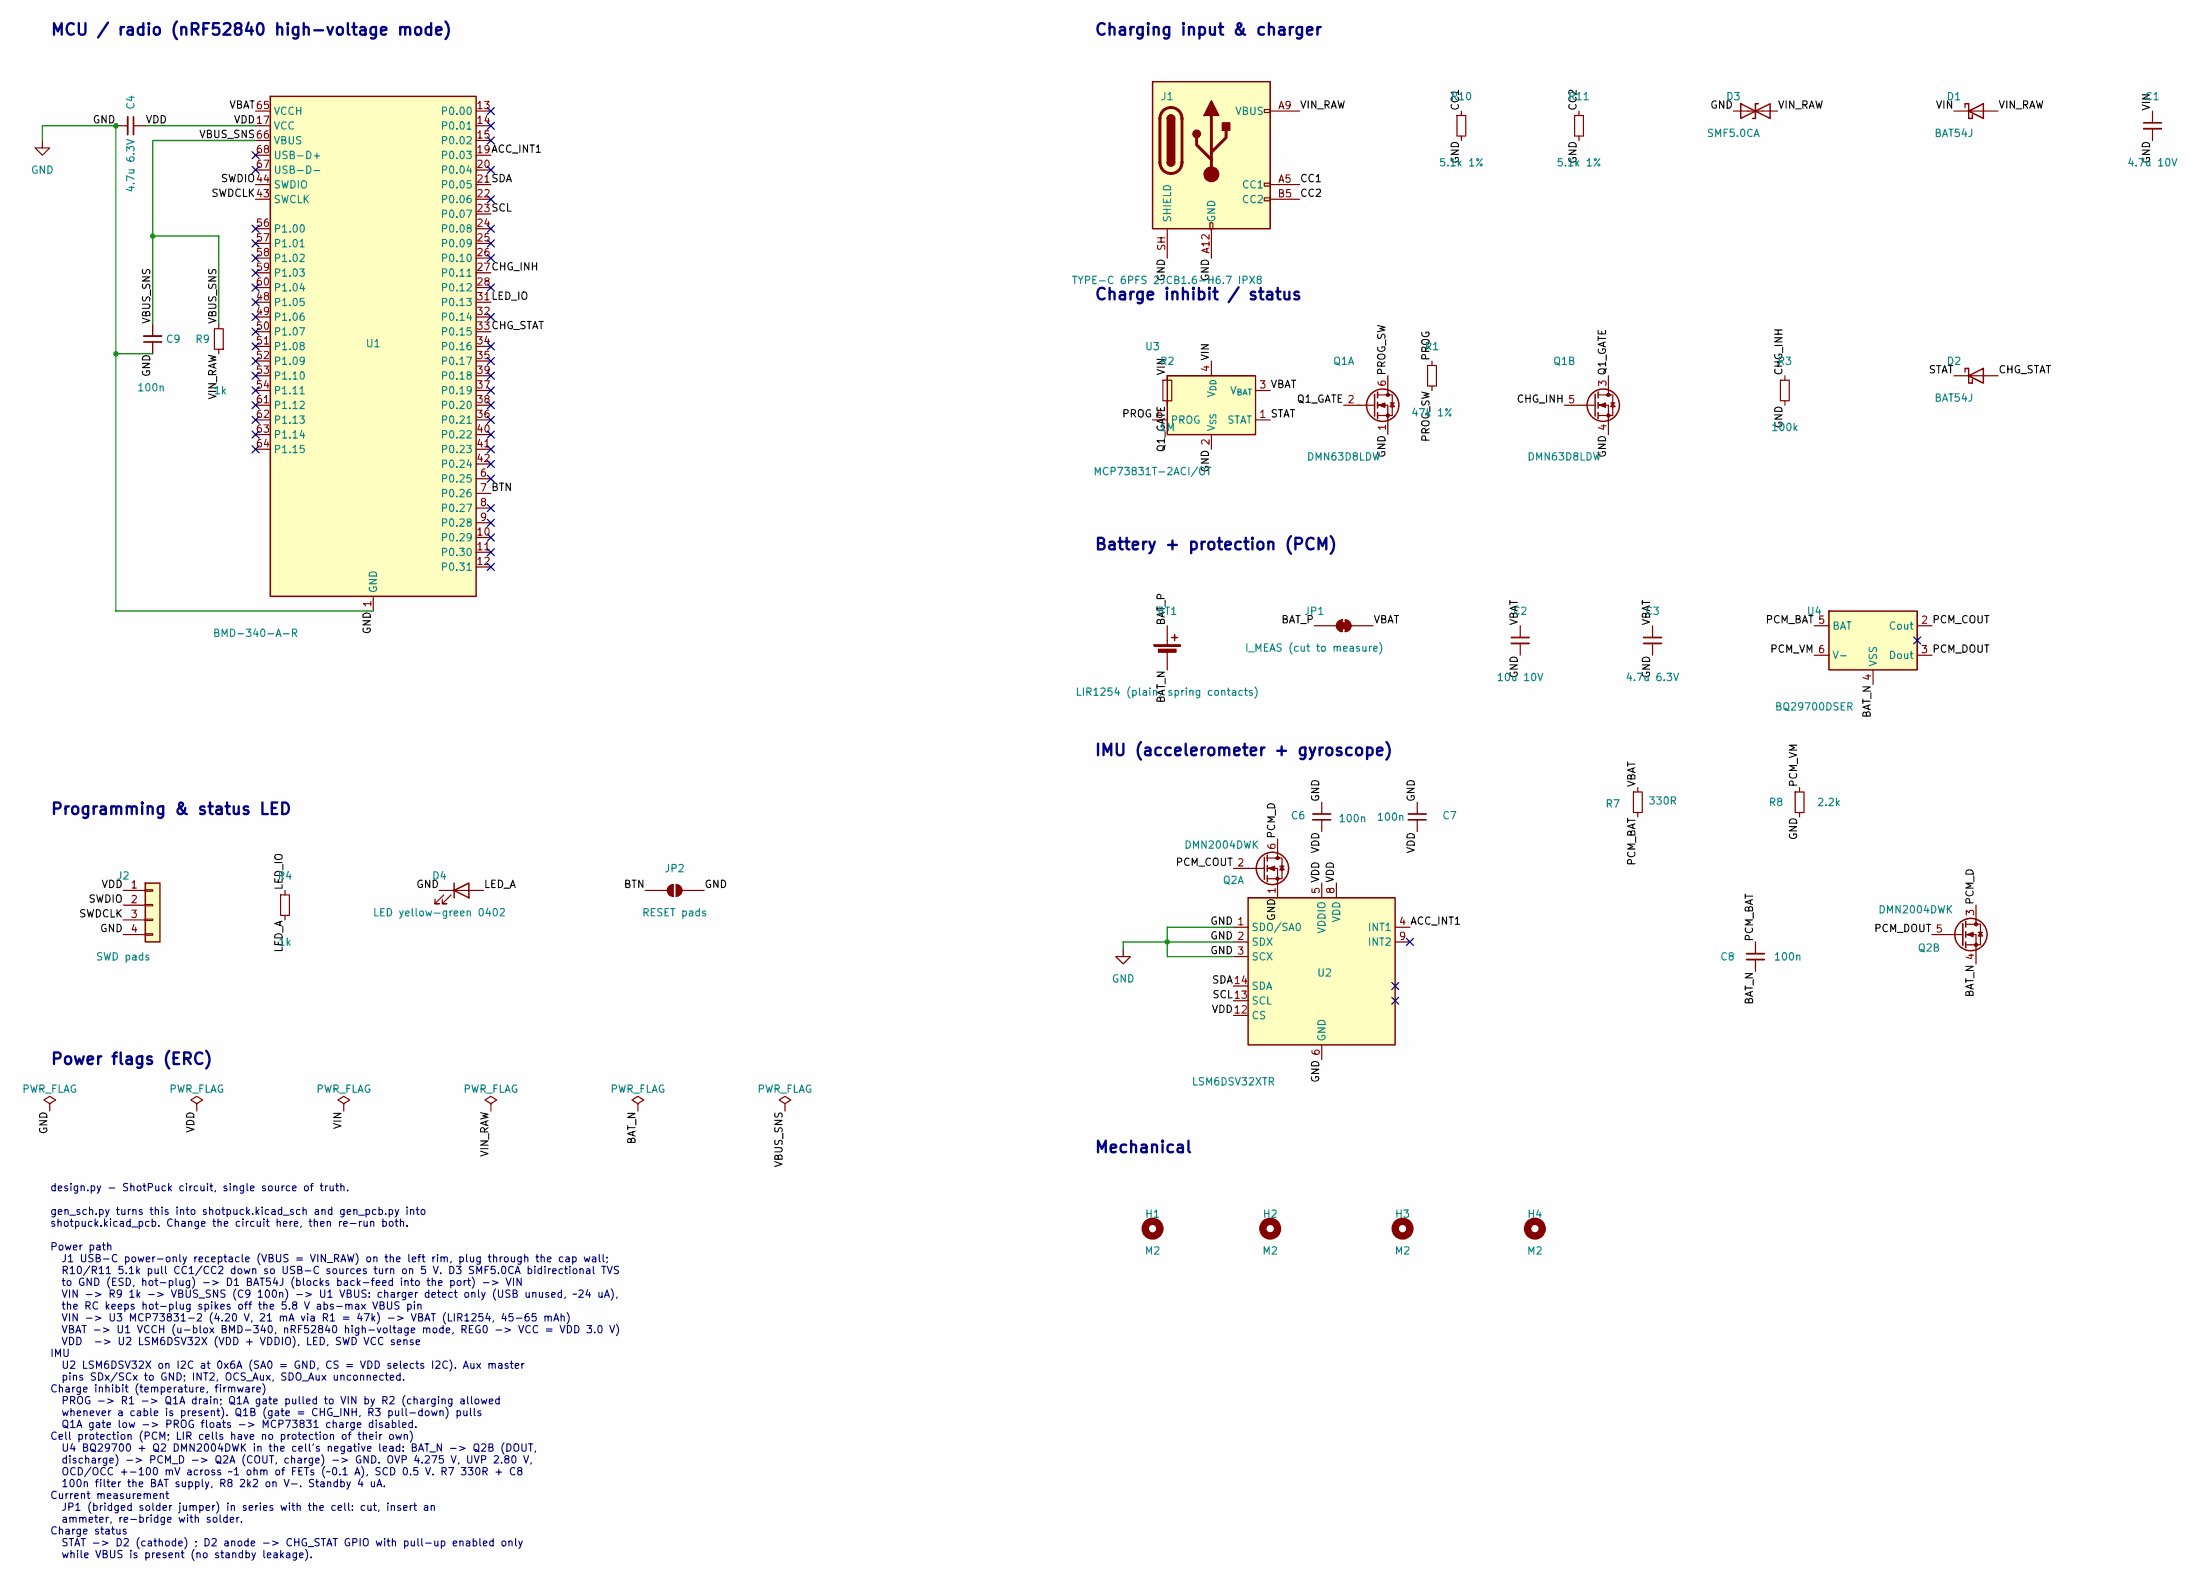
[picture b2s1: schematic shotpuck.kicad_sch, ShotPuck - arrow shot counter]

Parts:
BT1: LIR1254 (plain, spring contacts); LIR1254_Contacts_Edit
C1: 4.7u 10V; C_0603_1608Metric
C2: 10u 10V; C_0603_1608Metric
C3, C4: 4.7u 6.3V; C_0402_1005Metric
C6, C7, C8, C9: 100n; C_0402_1005Metric
D1, D2: BAT54J; D_SOD-323F
D3: SMF5.0CA; D_SOD-123F
D4: LED yellow-green 0402; LED_0402_1005Metric
H1, H2, H3, H4: M2; MountingHole_2.4mm_NPTH
J1: TYPE-C 6PFS 2JCB1.6-H6.7 IPX8; USB_C_Receptacle_ShouHan_TYPE-C-6PFS-2JCB1.6-H6.7_IPX8
J2: SWD pads; SWD_Pads_1x4_P2.54
JP1: I_MEAS (cut to measure); SolderJumper-2_P1.3mm_Bridged_Pad1.0x1.5mm
JP2: RESET pads; TweezerPads_2x0.8mm_Gap0.4mm
Q1: DMN63D8LDW; SOT-363_SC-70-6
Q2: DMN2004DWK; SOT-363_SC-70-6
R1: 47k 1%; R_0402_1005Metric
R2: 1M; R_0402_1005Metric
R3: 100k; R_0402_1005Metric
R4, R9: 1k; R_0402_1005Metric
R7: 330R; R_0402_1005Metric
R8: 2.2k; R_0402_1005Metric
R10, R11: 5.1k 1%; R_0402_1005Metric
U1: BMD-340-A-R; u-blox_BMD-340
U2: LSM6DSV32XTR; LGA-14_3x2.5mm_P0.5mm_LayoutBorder3x4y
U3: MCP73831T-2ACI/OT; SOT-23-5
U4: BQ29700DSER; WSON-6_1.5x1.5mm_P0.5mm

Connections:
/ACC_INT1: U1.19 (P0.03), U2.4 (INT1)
/BAT_N: BT1.2 (-), C8.2, Q2.4 (S), U4.4 (VSS)
/BAT_P: BT1.1 (+), JP1.1 (A)
/BTN: JP2.1 (A), U1.7 (P0.26)
/CC1: J1.A5 (CC1), R10.1
/CC2: J1.B5 (CC2), R11.1
/CHG_INH: Q1.5 (G), R3.1, U1.27 (P0.11)
/CHG_STAT: D2.2 (A), U1.33 (P0.15)
/GND: C1.2, C2.2, C3.2, C4.2, C6.2, C7.2, C9.2, D3.1 (A1), D4.1 (K), J1.A12 (GND), J1.B12 (GND), J1.SH (SHIELD), J2.4, JP2.2 (B), Q1.1 (S), Q1.4 (S), Q2.1 (S), R3.2, R8.2, R10.2, R11.2, U1.1 (GND), U1.2 (GND), U1.3 (GND), U1.4 (GND), U1.5 (GND), U1.16 (GND), U1.18 (GND), U1.29 (GND), U1.30 (GND), U1.45 (GND), U1.46 (GND), U1.47 (GND), U1.55 (GND), U2.1 (SDO/SA0), U2.2 (SDX), U2.3 (SCX), U2.6 (GND), U2.7 (GND), U3.2 (V_{SS})
/LED_A: D4.2 (A), R4.2
/LED_IO: R4.1, U1.31 (P0.13)
/PCM_BAT: C8.1, R7.2, U4.5 (BAT)
/PCM_COUT: Q2.2 (G), U4.2 (Cout)
/PCM_D: Q2.3 (D), Q2.6 (D)
/PCM_DOUT: Q2.5 (G), U4.3 (Dout)
/PCM_VM: R8.1, U4.6 (V-)
/PROG: R1.1, U3.5 (PROG)
/PROG_SW: Q1.6 (D), R1.2
/Q1_GATE: Q1.2 (G), Q1.3 (D), R2.2
/SCL: U1.23 (P0.07), U2.13 (SCL)
/SDA: U1.21 (P0.05), U2.14 (SDA)
/STAT: D2.1 (K), U3.1 (STAT)
/SWDCLK: J2.3, U1.43 (SWCLK)
/SWDIO: J2.2, U1.44 (SWDIO)
/VBAT: C2.1, C3.1, JP1.2 (B), R7.1, U1.65 (VCCH), U3.3 (V_{BAT})
/VBUS_SNS: C9.1, R9.2, U1.66 (VBUS)
/VDD: C4.1, C6.1, C7.1, J2.1, U1.17 (VCC), U2.5 (VDDIO), U2.8 (VDD), U2.12 (CS)
/VIN: C1.1, D1.1 (K), R2.1, U3.4 (V_{DD})
/VIN_RAW: D1.2 (A), D3.2 (A2), J1.A9 (VBUS), J1.B9 (VBUS), R9.1

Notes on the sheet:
Charging input & charger
MCU / radio (nRF52840 high-voltage mode)
IMU (accelerometer + gyroscope)
Mechanical
Power flags (ERC)
Programming & status LED
Charge inhibit / status
Battery + protection (PCM)
design.py - ShotPuck circuit, single source of truth. gen_sch.py turns this into shotpuck.kicad_sch and gen_pcb.py into shotpuck.kicad_pcb. Change the circuit here, then re-run both. Power path J1 USB-C power-only receptacle (VBUS = VIN_RAW) on the left rim, plug through the cap wall; R10/R11 5.1k 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

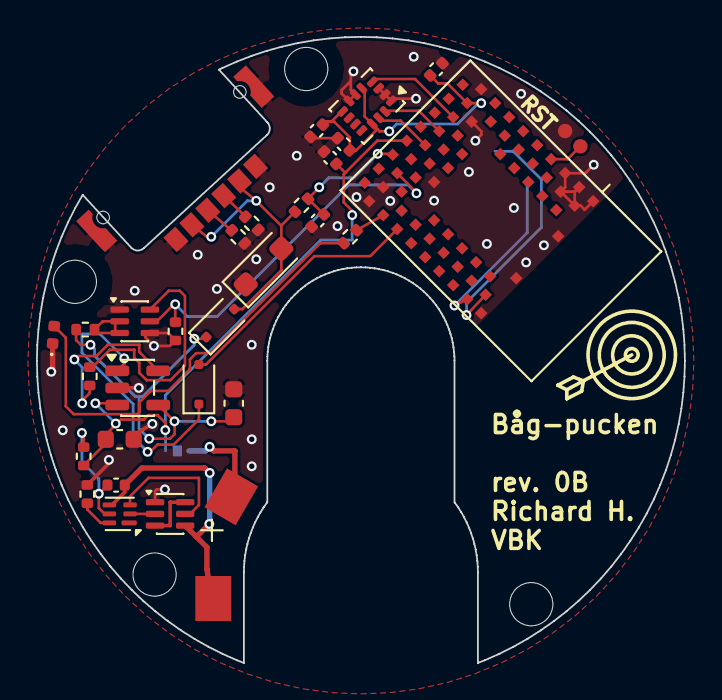
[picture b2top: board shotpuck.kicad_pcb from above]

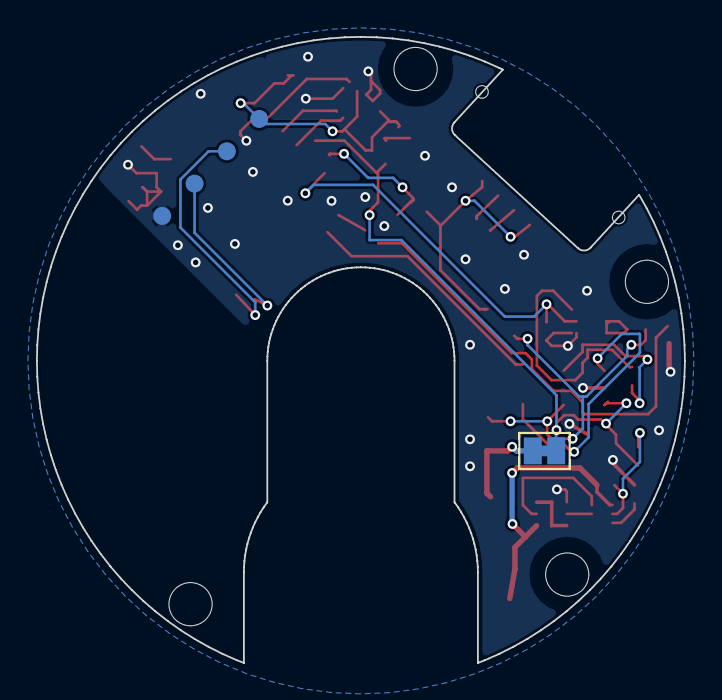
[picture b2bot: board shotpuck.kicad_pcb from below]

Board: 2 copper layers, 36.0 x 34.8 mm, 36 parts (2 on the bottom side), 29 nets.

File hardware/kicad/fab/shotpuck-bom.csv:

Qty,References,Value,Footprint,Manufacturer,MPN,DNP
1,BT1,"LIR1254 (plain, spring contacts)",LIR1254_Contacts_Edit,generic,"LIR1254 3.6-3.7 V 45-65 mAh, no tabs - pick a maker with a datasheet",
1,C1,4.7u 10V,C_0603_1608Metric,Murata,GRM188R61A475KE15D,
1,C2,10u 10V,C_0603_1608Metric,Samsung,CL10A106KP8NNNC,
2,C3 C4,4.7u 6.3V,C_0402_1005Metric,Murata,GRM155R60J475ME47D,
4,C6 C7 C8 C9,100n,C_0402_1005Metric,Murata,GRM155R71C104KA88D,
2,D1 D2,BAT54J,D_SOD-323F,Nexperia,"BAT54J,115",
1,D3,SMF5.0CA,D_SOD-123F,Littelfuse,SMF5.0CA (second sources: MDD / FUXINSEMI SMF5.0CA),
1,D4,LED yellow-green 0402,LED_0402_1005Metric,XINGLIGHT,"XL-1005SYGC (AlGaInP 572 nm, Vf ~2 V)",
1,J1,TYPE-C 6PFS 2JCB1.6-H6.7 IPX8,USB_C_Receptacle_ShouHan_TYPE-C-6PFS-2JCB1.6-H6.7_IPX8,SHOU HAN,waterproof USB-C 6P power-only (LCSC C3020041),
1,J2,SWD pads,SWD_Pads_1x4_P2.54,-,"4 bottom test pads (VDD, SWDIO, SWDCLK, GND) at 2.54 mm: program with a 4-pin pogo jig",
1,JP1,I_MEAS (cut to measure),SolderJumper-2_P1.3mm_Bridged_Pad1.0x1.5mm,,,
1,JP2,RESET pads,TweezerPads_2x0.8mm_Gap0.4mm,-,"2 bare top pads (BTN, GND), copper only: bridge with tweezers for a factory reset",
1,Q1,DMN63D8LDW,SOT-363_SC-70-6,Diodes Inc,DMN63D8LDW-7,
1,Q2,DMN2004DWK,SOT-363_SC-70-6,Diodes Inc,DMN2004DWK-7,
1,R1,47k 1%,R_0402_1005Metric,UNI-ROYAL,0402WGF4702TCE,
2,R10 R11,5.1k 1%,R_0402_1005Metric,UNI-ROYAL,0402WGF5101TCE,
1,R2,1M,R_0402_1005Metric,Yageo,RC0402FR-071ML,
1,R3,100k,R_0402_1005Metric,Yageo,RC0402FR-07100KL,
2,R4 R9,1k,R_0402_1005Metric,Yageo,RC0402FR-071KL,
1,R7,330R,R_0402_1005Metric,Yageo,RC0402FR-07330RL,
1,R8,2.2k,R_0402_1005Metric,Yageo,RC0402FR-072K2L,
1,U1,BMD-340-A-R,u-blox_BMD-340,u-blox,BMD-340-A-R-10,
1,U2,LSM6DSV32XTR,LGA-14_3x2.5mm_P0.5mm_LayoutBorder3x4y,STMicroelectronics,LSM6DSV32XTR,
1,U3,MCP73831T-2ACI/OT,SOT-23-5,Microchip,MCP73831T-2ACI/OT,
1,U4,BQ29700DSER,WSON-6_1.5x1.5mm_P0.5mm,Texas Instruments,BQ29700DSER,
